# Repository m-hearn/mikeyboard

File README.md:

# mikeyboard

kicad files - pcb design for 36key - reversible pcb for left and right sides - arduino
vial-qmk config

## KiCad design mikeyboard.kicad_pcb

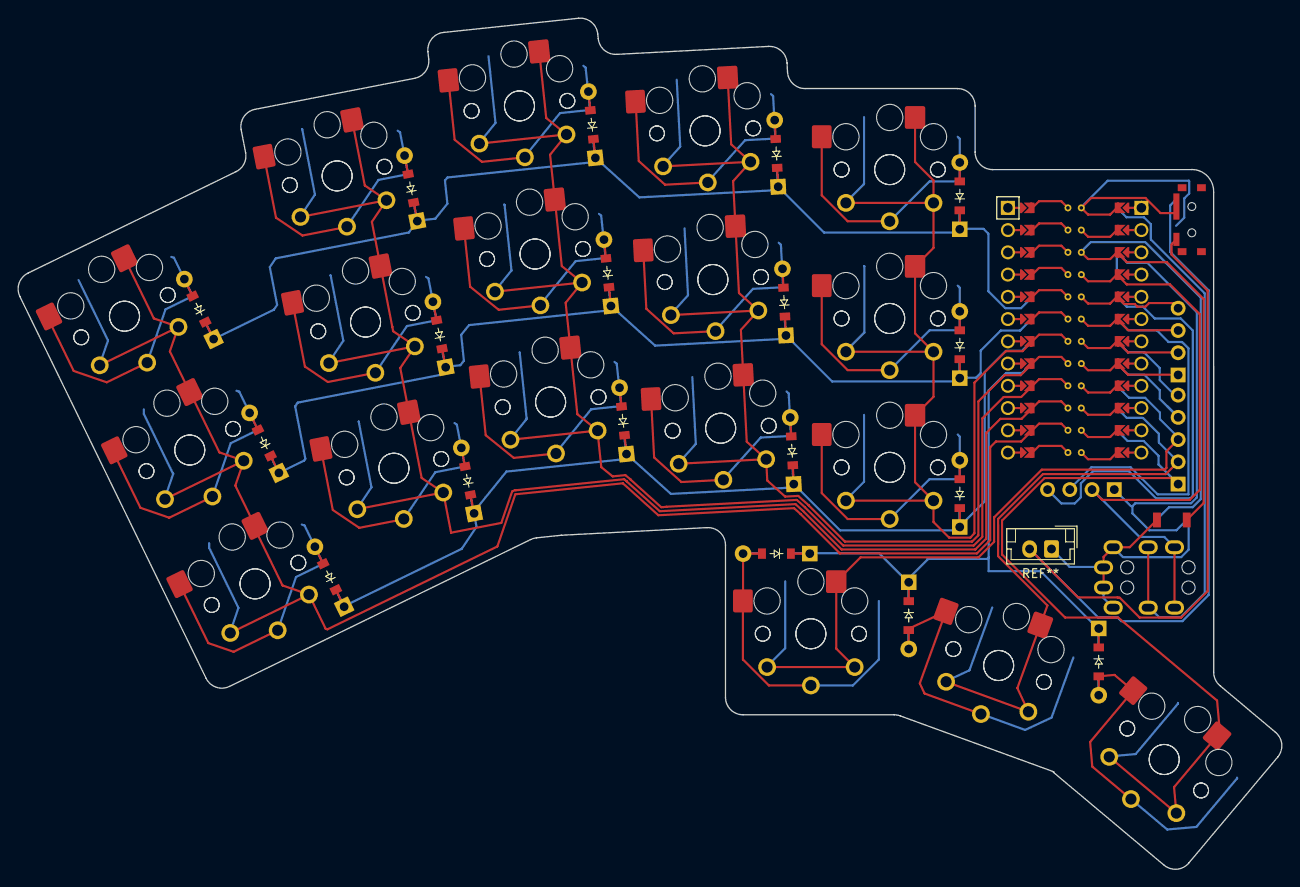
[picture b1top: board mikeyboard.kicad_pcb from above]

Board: 2 copper layers, 144.3 x 97.2 mm, 59 parts (0 on the bottom side), 32 nets.

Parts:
D1, D2, D3, D4, D5, D6, D7, D8, D9, D10, D11, D12, D13, D14, D15, D16, D17, D18: ComboDiode
H1: Hdr; PinHeader_1x05_P2.54mm_Vertical
MCU1: ProMicro
OLED1, OLED2: OLED; OLED_headers
S1, S2, S3, S4, S5, S6, S7, S8, S9, S10, S11, S12, S13, S14, S15, S16, S17, S18, S19, S20, S21, S22, S23, S24, S25, S26, S27, S28, S29, S30, S31, S32, S33, S34, S35, S36: PG1350
TRRS1: TRRS-PJ-320A-dual

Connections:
GND: MCU1.2, MCU1.21, MCU1.22, OLED1.1, TRRS1.1, TRRS1.2
P4: H1.4, MCU1.18, S13.1, S14.1, S15.1, S31.1, S32.1, S33.1
P5: H1.3, MCU1.17, S10.1, S11.1, S12.1, S28.1, S29.1, S30.1
P6: H1.2, MCU1.16, S7.1, S8.1, S9.1, S16.1, S25.1, S26.1, S27.1, S34.1
P7: H1.1, MCU1.15, S4.1, S5.1, S6.1, S17.1, S22.1, S23.1, S24.1, S35.1
P8: H1.1, MCU1.14, S1.1, S2.1, S3.1, S18.1, S19.1, S20.1, S21.1, S36.1
P18: D16.1, D17.1, D18.1, MCU1.8, OLED2.1
P19: D1.1, D4.1, D7.1, D10.1, D13.1, MCU1.7, OLED2.2
P20: D2.1, D5.1, D8.1, D11.1, D14.1, MCU1.6, OLED2.3
P21: D3.1, D6.1, D9.1, D12.1, D15.1, MCU1.5, OLED2.4
SCL: MCU1.19, OLED1.3
SDA: MCU1.20, OLED1.4
Tx: MCU1.24, TRRS1.3
VCC: MCU1.4, OLED1.2, TRRS1.4
far_thumb: D18.2, S18.2, S36.2
home_thumb: D17.2, S17.2, S35.2
index_bottom: D10.2, S10.2, S28.2
index_home: D11.2, S11.2, S29.2
index_top: D12.2, S12.2, S30.2
inner_bottom: D13.2, S13.2, S31.2
inner_home: D14.2, S14.2, S32.2
inner_top: D15.2, S15.2, S33.2
middle_bottom: D7.2, S7.2, S25.2
middle_home: D8.2, S8.2, S26.2
middle_top: D9.2, S9.2, S27.2
near_thumb: D16.2, S16.2, S34.2
pinkie_bottom: D1.2, S1.2, S19.2
pinkie_home: D2.2, S2.2, S20.2
pinkie_top: D3.2, S3.2, S21.2
ring_bottom: D4.2, S4.2, S22.2
ring_home: D5.2, S5.2, S23.2
ring_top: D6.2, S6.2, S24.2

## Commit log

2024-06-29 Add files via upload
    Initial commit
